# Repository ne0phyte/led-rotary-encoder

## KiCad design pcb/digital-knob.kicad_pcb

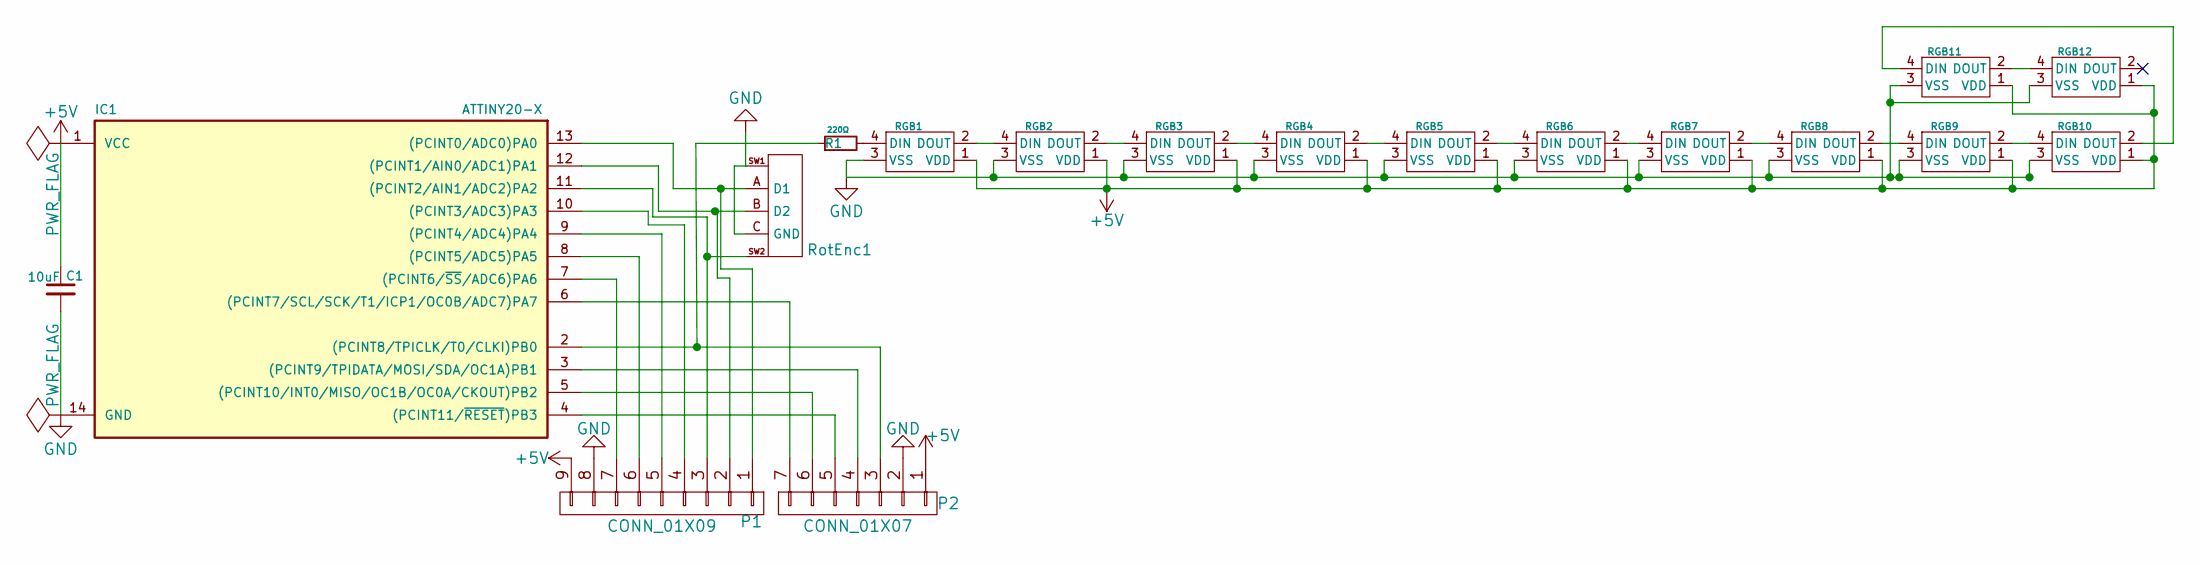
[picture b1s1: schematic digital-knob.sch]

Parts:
C1: 10uF; C_1206
IC1: ATTINY20-X; SSOP-14
P1: CONN_01X09
P2: CONN_01X07
R1: 220Ω; R_1206
RGB1, RGB2, RGB3, RGB4, RGB5, RGB6, RGB7, RGB8, RGB9, RGB10, RGB11, RGB12: RGB_LED_5050; LED_WS2812B-PLCC4
RotEnc1: Rotary_Encoder; ALPS_STEC12E08

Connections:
+5V: C1.1, IC1.1 (VCC), P1.9, P2.1, RGB1.1 (VDD), RGB2.1 (VDD), RGB3.1 (VDD), RGB4.1 (VDD), RGB5.1 (VDD), RGB6.1 (VDD), RGB7.1 (VDD), RGB8.1 (VDD), RGB9.1 (VDD), RGB10.1 (VDD), RGB11.1 (VDD), RGB12.1 (VDD)
GND: C1.2, IC1.14 (GND), P1.8, P2.2, RGB1.3 (VSS), RGB2.3 (VSS), RGB3.3 (VSS), RGB4.3 (VSS), RGB5.3 (VSS), RGB6.3 (VSS), RGB7.3 (VSS), RGB8.3 (VSS), RGB9.3 (VSS), RGB10.3 (VSS), RGB11.3 (VSS), RGB12.3 (VSS), RotEnc1.C (GND), RotEnc1.SW1
unnamed: IC1.2 ((PCINT8/TPICLK/T0/CLKI)PB0), P2.3, R1.1
unnamed: IC1.3 ((PCINT9/TPIDATA/MOSI/SDA/OC1A)PB1), P2.4
unnamed: IC1.4 ((PCINT11/~RESET~)PB3), P2.5
unnamed: IC1.5 ((PCINT10/INT0/MISO/OC1B/OC0A/CKOUT)PB2), P2.6
unnamed: IC1.6 ((PCINT7/SCL/SCK/T1/ICP1/OC0B/ADC7)PA7), P2.7
unnamed: IC1.7 ((PCINT6/~SS~/ADC6)PA6), P1.7
unnamed: IC1.8 ((PCINT5/ADC5)PA5), P1.6
unnamed: IC1.9 ((PCINT4/ADC4)PA4), P1.5
unnamed: IC1.10 ((PCINT3/ADC3)PA3), P1.4
unnamed: IC1.11 ((PCINT2/AIN1/ADC2)PA2), P1.3, RotEnc1.SW2
unnamed: IC1.12 ((PCINT1/AIN0/ADC1)PA1), P1.2, RotEnc1.B (D2)
unnamed: IC1.13 ((PCINT0/ADC0)PA0), P1.1, RotEnc1.A (D1)
unnamed: R1.2, RGB1.4 (DIN)
unnamed: RGB1.2 (DOUT), RGB2.4 (DIN)
unnamed: RGB2.2 (DOUT), RGB3.4 (DIN)
unnamed: RGB3.2 (DOUT), RGB4.4 (DIN)
unnamed: RGB4.2 (DOUT), RGB5.4 (DIN)
unnamed: RGB5.2 (DOUT), RGB6.4 (DIN)
unnamed: RGB6.2 (DOUT), RGB7.4 (DIN)
unnamed: RGB7.2 (DOUT), RGB8.4 (DIN)
unnamed: RGB8.2 (DOUT), RGB9.4 (DIN)
unnamed: RGB10.2 (DOUT), RGB11.4 (DIN)
unnamed: RGB9.2 (DOUT), RGB10.4 (DIN)
unnamed: RGB11.2 (DOUT), RGB12.4 (DIN)

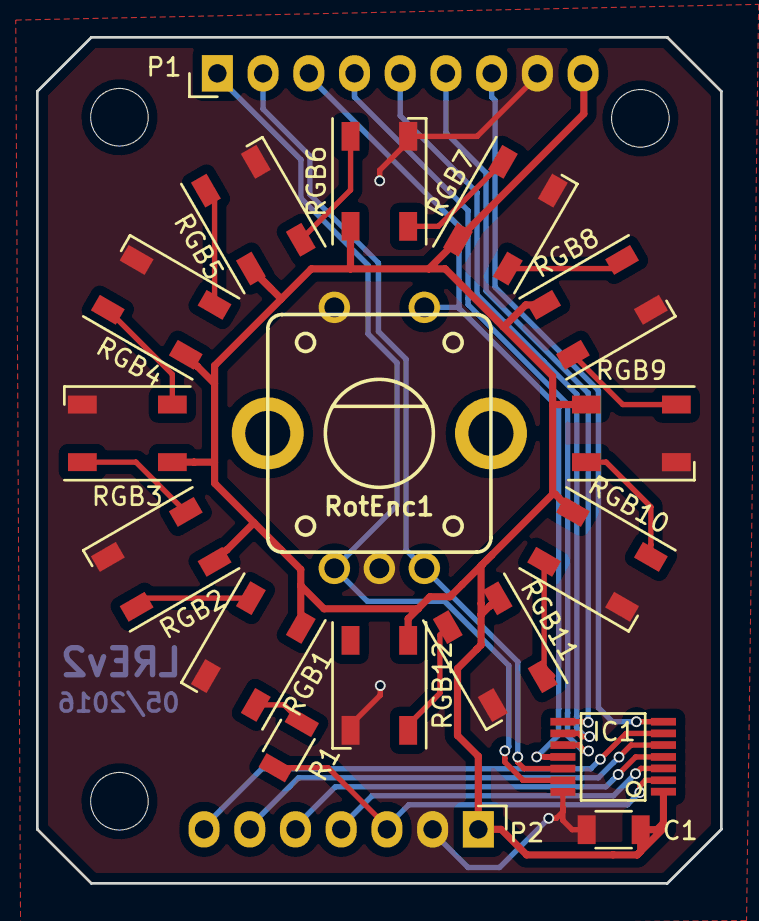
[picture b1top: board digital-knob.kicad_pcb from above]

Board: 2 copper layers, 38.0 x 47.0 mm, 21 parts (0 on the bottom side), 26 nets.

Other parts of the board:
H1, H2, H3: MountingHole_3.2mm_M3

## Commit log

2016-04-01 Added ws2812 library
2016-04-30 added some pictures
2016-05-01 Initial version of v2 single encoder pcb
2016-05-02 Removed silk screen drawings of pin header out of pcb bounds
2016-05-13 Updated gerber file zip
2016-05-20 Some test code
2016-05-21 Added i2c bus
2016-05-23 Added better rotary encoder driver
2016-05-23 Implemented blending and i2c commands
2016-05-23 I2C not working for some reason
